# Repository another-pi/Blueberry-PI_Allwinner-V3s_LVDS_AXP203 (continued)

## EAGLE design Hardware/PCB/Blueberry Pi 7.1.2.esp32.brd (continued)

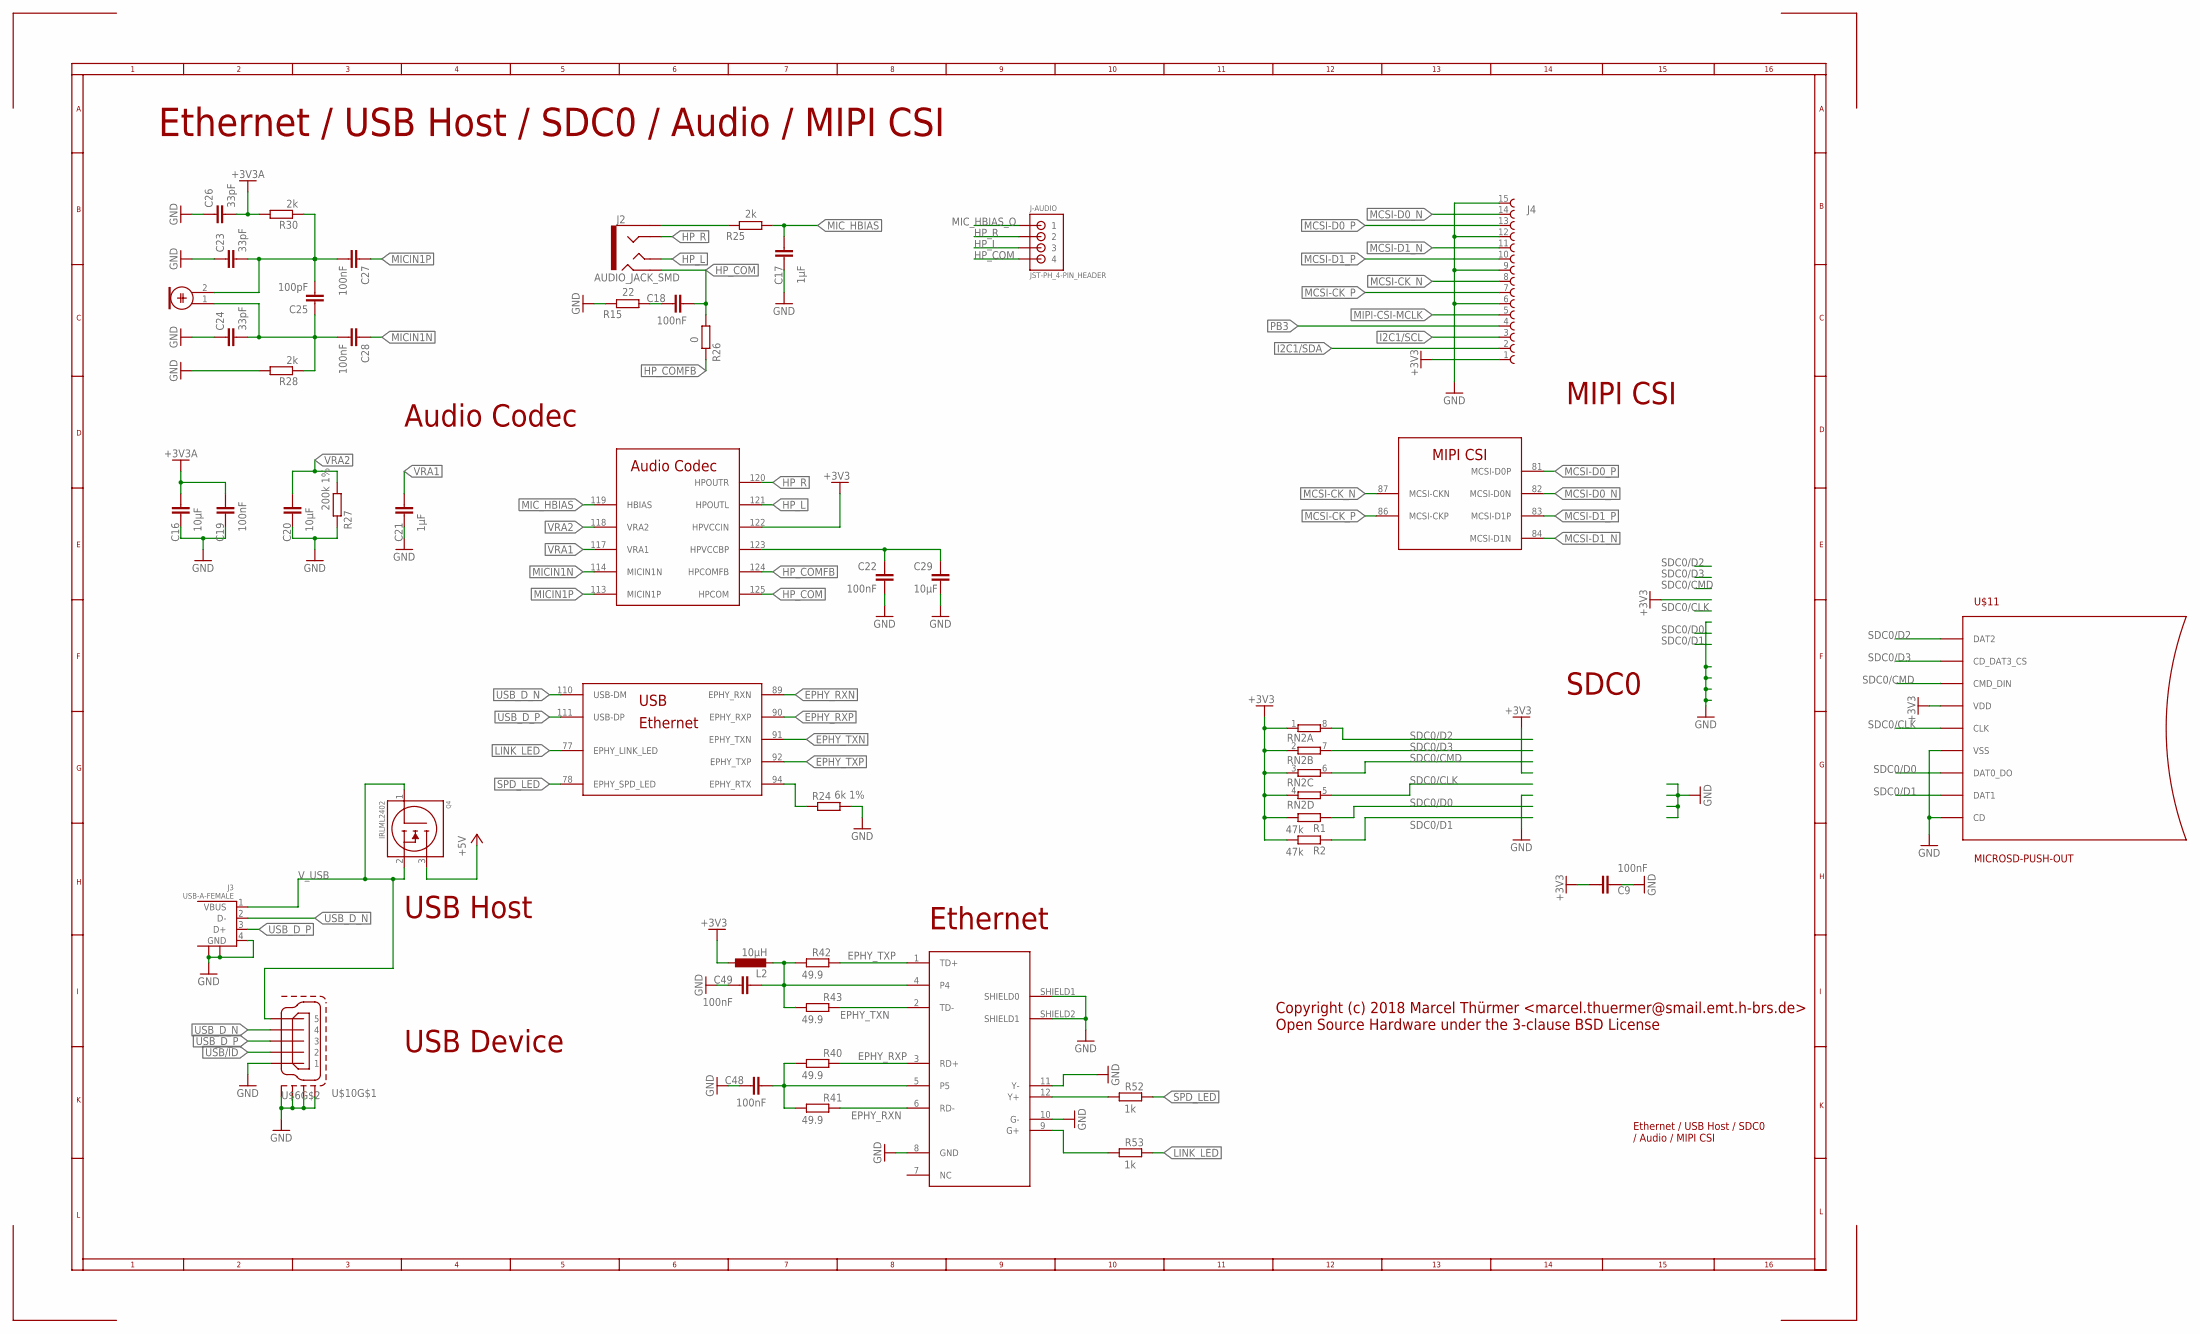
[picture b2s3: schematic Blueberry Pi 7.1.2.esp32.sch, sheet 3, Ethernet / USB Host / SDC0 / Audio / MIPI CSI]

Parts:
C9, C18, C19, C22, C27, C28, C48, C49: 100nF; C0603
C16, C20, C29: 10µF; C0805
C17, C21: 1µF; C0603
C23, C24, C26: 33pF; C0603
C25: 100pF; C0603
J2: AUDIO_JACK_SMD; AUDIO_JACK_3.5MM_TRRS_SMD_RA
J3: USB-A-FEMALE
J4: 68611514122
J-AUDIO: JST-PH_4-PIN_HEADER; JST_B4B-PH_HEADER
L2: 10µH; L0805
MIC: ELECTRET_MICROPHON-F6035AP; F6035AP
Q4: IRLML2402; SOT23
R1, R2: 47k; R0603
R15: 22; R0603
R24: 6k 1%; R0603
R25, R28, R30: 2k; R0603
R26: 0; R0603
R27: 200k 1%; R0603
R40, R41, R42, R43: 49.9; R0603
R52, R53: 1k; R0603
RN2: 4R-NEXB38V; EXB38V
U$1: V3S; QFP-128
U$3: HR911105A; RJ45
U$6, U$10: MICRO-USB-SHIELD-ZX62R-B-5P; ZX62R-B-5P
U$11: MICROSD-PUSH-OUT

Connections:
+3V3: C9.1, J4.1 (15), L2.1, R1.2, R2.2, RN2.1, RN2.2 (1), RN2.3 (1), RN2.4 (1), U$1.122 (HPVCCIN), U$11.4 (VDD); also elsewhere on the board
+3V3A: C16.2, C19.2, C26.2, R30.2; also elsewhere on the board
+5V: Q4.3 (DRAIN); also elsewhere on the board
EPHY_RXN: R41.1, U$1.89 (EPHY_RXN), U$3.6 (RD-)
EPHY_RXP: R40.1, U$1.90 (EPHY_RXP), U$3.3 (RD+)
EPHY_TXN: R43.1, U$1.91 (EPHY_TXN), U$3.2 (TD-)
EPHY_TXP: R42.1, U$1.92 (EPHY_TXP), U$3.1 (TD+)
GND: C9.2, C16.1, C17.2, C19.1, C20.1, C21.1, C22.2, C23.1, C24.1, C26.1, C29.1, C48.2, C49.2, J3.4 (GND), J3.P$1, J3.P$2, J4.6 (10), J4.9 (7), J4.12 (4), J4.15 (1), R15.1, R24.2, R27.1, R28.2, U$3.8 (GND), U$3.10 (G-), U$3.11 (Y-), U$3.SHIELD1 (SHIELD0), U$3.SHIELD2 (SHIELD1), U$6.1, U$10.M1 (S1), U$10.M2 (S2), U$10.M3 (S3), U$10.M4 (S4), U$11.6 (VSS), U$11.CD, U$11.G1 (VSS), U$11.G2 (VSS), U$11.G3 (VSS), U$11.G4 (VSS); also elsewhere on the board
HP_COM: C18.2, J2.RING2, J-AUDIO.P4 (4), R26.2, U$1.125 (HPCOM)
HP_COMFB: R26.1, U$1.124 (HPCOMFB)
HP_L: J2.TIP, J-AUDIO.P3 (3), U$1.121 (HPOUTL)
HP_R: J2.RING1, J-AUDIO.P2 (2), U$1.120 (HPOUTR)
I2C1/SCL: J4.3 (13); also elsewhere on the board
I2C1/SDA: J4.2 (14); also elsewhere on the board
LINK_LED: R53.1, U$1.77 (EPHY_LINK_LED)
MCSI-CK_N: J4.8, U$1.87 (MCSI-CKN)
MCSI-CK_P: J4.7 (9), U$1.86 (MCSI-CKP)
MCSI-D0_N: J4.14 (2), U$1.82 (MCSI-D0N)
MCSI-D0_P: J4.13 (3), U$1.81 (MCSI-D0P)
MCSI-D1_N: J4.11 (5), U$1.84 (MCSI-D1N)
MCSI-D1_P: J4.10 (6), U$1.83 (MCSI-D1P)
MICIN1N: C28.1, U$1.114 (MICIN1N)
MICIN1P: C27.1, U$1.113 (MICIN1P)
MIC_HBIAS: C17.1, R25.2, U$1.119 (HBIAS)
MIC_HBIAS_O: J2.EARTH, J-AUDIO.P1 (1), R25.1
MIPI-CSI-MCLK: J4.5 (11); also elsewhere on the board
unnamed: R24.1, U$1.94 (EPHY_RTX)
unnamed: R53.2, U$3.9 (G+)
unnamed: R52.2, U$3.12 (Y+)
unnamed: C49.1, L2.2, R42.2, R43.2, U$3.4
unnamed: C48.1, R40.2, R41.2, U$3.5
unnamed: C22.1, C29.2, U$1.123 (HPVCCBP)
unnamed: C18.1, R15.2
unnamed: C23.2, C25.2, C27.2, MIC.2, R30.1
unnamed: C24.2, C25.1, C28.2, MIC.1, R28.1
PB3: J4.4 (12); also elsewhere on the board
SDC0/CLK: RN2.5 (2), U$11.5 (CLK); also elsewhere on the board
SDC0/CMD: RN2.6 (2), U$11.3 (CMD_DIN); also elsewhere on the board
SDC0/D0: R1.1, U$11.7 (DAT0_DO); also elsewhere on the board
SDC0/D1: R2.1, U$11.8 (DAT1); also elsewhere on the board
SDC0/D2: RN2.8 (2), U$11.1 (DAT2); also elsewhere on the board
SDC0/D3: RN2.7 (2), U$11.2 (CD_DAT3_CS); also elsewhere on the board
SPD_LED: R52.1, U$1.78 (EPHY_SPD_LED)
USB/ID: U$6.2; also elsewhere on the board
USB_D_N: J3.2 (D-), U$1.110 (USB-DM), U$6.4
USB_D_P: J3.3 (D+), U$1.111 (USB-DP), U$6.3
VRA1: C21.2, U$1.117 (VRA1)
VRA2: C20.2, R27.2, U$1.118 (VRA2)
V_USB: J3.1 (VBUS), Q4.1 (GATE), Q4.2 (SOURCE), U$6.5

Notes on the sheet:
Ethernet / USB Host / SDC0 / Audio / MIPI CSI
USB Host
Audio Codec
MIPI CSI
Ethernet
SDC0
Copyright (c) 2018 Marcel Thürmer <marcel.thuermer@smail.emt.h-brs.de> Open Source Hardware under the 3-clause BSD License
USB Device
Ethernet / USB Host / SDC0 / Audio / MIPI CSI

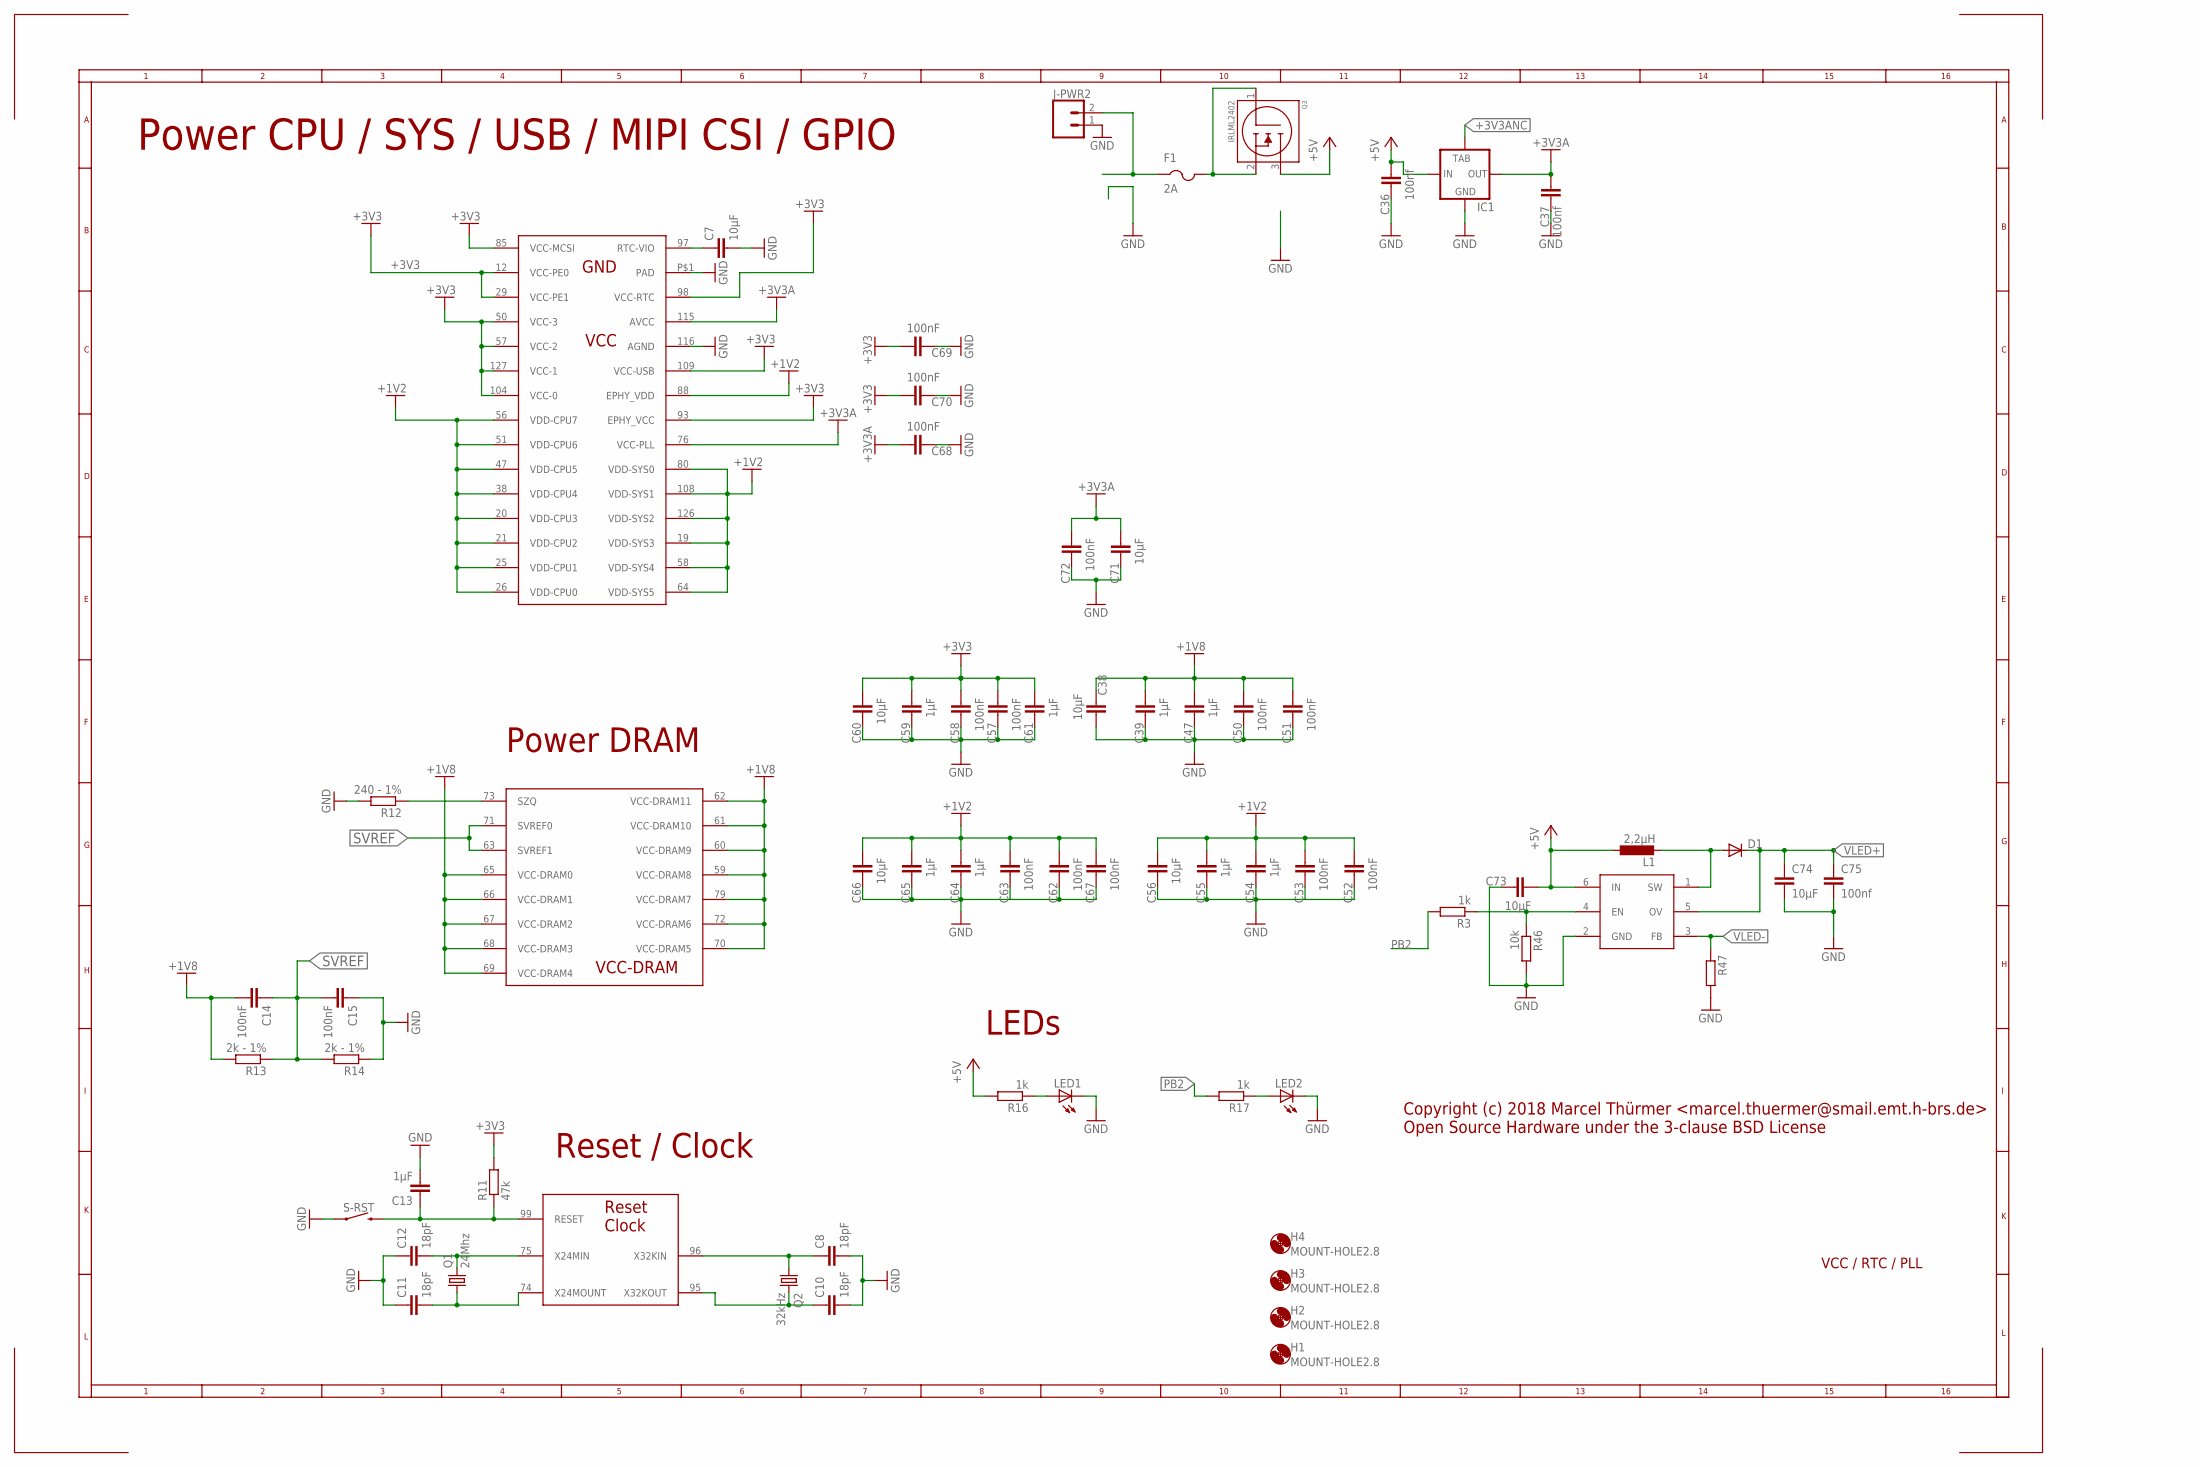
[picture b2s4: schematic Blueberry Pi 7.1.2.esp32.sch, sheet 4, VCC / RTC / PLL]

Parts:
C7, C66, C73, C74: 10µF; C0805
C8, C10, C11, C12: 18pF; C0603
C13, C39, C47, C55, C64, C65: 1µF; C0603
C14, C15, C51, C53, C57, C58, C62, C67, C68, C70, C72: 100nF; C0603
C36, C37, C75: 100nf; C0603
C38, C56, C60, C71: 10µF; C0603
C50, C52, C63, C69: 100nF; C0805
C54, C59, C61: 1µF; C0805
D1: DIODE-SOD323-W; SOD323-W
F1: 2A; R1206
H1, H2, H3, H4: MOUNT-HOLE2.8; 2,8
IC1: LM1117; SOT223
J-PWR2: CONN_02; 1X02
L1: 2,2µH; ODD-INDUCTOR
LED1, LED2: LEDCHIPLED_0805; CHIPLED_0805
Q1: 24Mhz; HC49U-V
Q2: 32kHz; TC38H
Q3: IRLML2402; SOT23
R3, R16, R17: 1k; R0603
R11: 47k; R0603
R12: 240 - 1%; R0603
R13, R14: 2k - 1%; R0603
R46: 10k; R0603
R47: R-EU_R0603; R0603
S-RST: SPARKFUN-SWITCHES_MOMENTARY-SWITCH-SPST-SMD-5.2-R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; SPARKFUN-SWITCHES_TACTILE_SWITCH_SMD_5.2MM
U$1: V3S; QFP-128
U$9: PT4101; SOT23-6

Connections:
5VNS: F1.1, J-PWR2.2
+1V2: C52.1, C53.1, C54.1, C55.1, C56.1, C62.1, C63.1, C64.1, C65.1, C66.1, C67.1, U$1.19 (VDD-SYS3), U$1.20 (VDD-CPU3), U$1.21 (VDD-CPU2), U$1.25 (VDD-CPU1), U$1.26 (VDD-CPU0), U$1.38 (VDD-CPU4), U$1.47 (VDD-CPU5), U$1.51 (VDD-CPU6), U$1.56 (VDD-CPU7), U$1.58 (VDD-SYS4), U$1.64 (VDD-SYS5), U$1.80 (VDD-SYS0), U$1.88 (EPHY_VDD), U$1.108 (VDD-SYS1), U$1.126 (VDD-SYS2); also elsewhere on the board
+1V8: C14.2, C38.2, C39.1, C47.1, C50.1, C51.1, R13.2, U$1.59 (VCC-DRAM8), U$1.60 (VCC-DRAM9), U$1.61 (VCC-DRAM10), U$1.62 (VCC-DRAM11), U$1.65 (VCC-DRAM0), U$1.66 (VCC-DRAM1), U$1.67 (VCC-DRAM2), U$1.68 (VCC-DRAM3), U$1.69 (VCC-DRAM4), U$1.70 (VCC-DRAM5), U$1.72 (VCC-DRAM6), U$1.79 (VCC-DRAM7); also elsewhere on the board
+3V3: C57.1, C58.1, C59.1, C60.1, C61.1, C69.1, C70.1, R11.2, U$1.12 (VCC-PE0), U$1.29 (VCC-PE1), U$1.50 (VCC-3), U$1.57 (VCC-2), U$1.85 (VCC-MCSI), U$1.93 (EPHY_VCC), U$1.98 (VCC-RTC), U$1.104 (VCC-0), U$1.109 (VCC-USB), U$1.127 (VCC-1); also elsewhere on the board
+3V3A: C37.1, C68.1, C71.1, C72.1, IC1.2 (OUT), U$1.76 (VCC-PLL), U$1.115 (AVCC); also elsewhere on the board
+3V3ANC: IC1.4 (IN1)
+5V: C36.1, C73.1, IC1.3 (IN), L1.P$1 (1), Q3.3 (DRAIN), R16.2, U$9.6 (IN); also elsewhere on the board
GND: C7.2, C8.2, C10.2, C11.1, C12.1, C13.2, C15.1, C36.2, C37.2, C38.1, C39.2, C47.2, C50.2, C51.2, C52.2, C53.2, C54.2, C55.2, C56.2, C57.2, C58.2, C59.2, C60.2, C61.2, C62.2, C63.2, C64.2, C65.2, C66.2, C67.2, C68.2, C69.2, C70.2, C71.2, C72.2, C73.2, C74.2, C75.2, IC1.1 (GND), J-PWR2.1, LED1.C, LED2.C, R12.2, R14.1, R46.2, R47.2, S-RST.1, S-RST.2 (1), U$1.116 (AGND), U$1.P$1 (PAD), U$9.2 (GND); also elsewhere on the board
unnamed: LED1.A, R16.1
unnamed: LED2.A, R17.1
unnamed: R3.1, R46.1, U$9.4 (EN)
unnamed: D1.A, L1.P$2 (2), U$9.1 (SW)
unnamed: C7.1, U$1.97 (RTC-VIO)
unnamed: C10.1, Q2.2, U$1.95 (X32KOUT)
unnamed: C8.1, Q2.1, U$1.96 (X32KIN)
unnamed: C11.2, Q1.1, U$1.74 (X24MOUNT)
unnamed: C12.2, Q1.2, U$1.75 (X24MIN)
unnamed: C13.1, R11.1, S-RST.3 (2), S-RST.4 (2), U$1.99 (RESET)
unnamed: R12.1, U$1.73 (SZQ)
PB2: R3.2, R17.2; also elsewhere on the board
SVREF: C14.1, C15.2, R13.1, R14.2, U$1.63 (SVREF1), U$1.71 (SVREF0)
VLED+: C74.1, C75.1, D1.C, U$9.5 (OV); also elsewhere on the board
VLED-: R47.1, U$9.3 (FB); also elsewhere on the board
V_PWR: F1.2, Q3.1 (GATE), Q3.2 (SOURCE)

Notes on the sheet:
VCC / RTC / PLL
Power CPU / SYS / USB / MIPI CSI / GPIO
Power DRAM
Copyright (c) 2018 Marcel Thürmer <marcel.thuermer@smail.emt.h-brs.de> Open Source Hardware under the 3-clause BSD License
Reset / Clock
LEDs

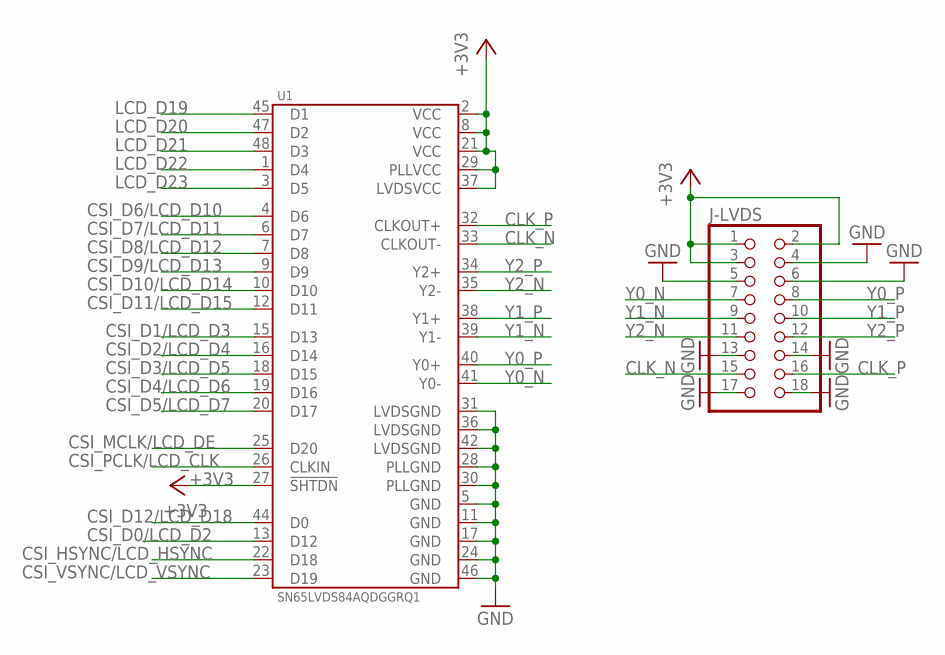
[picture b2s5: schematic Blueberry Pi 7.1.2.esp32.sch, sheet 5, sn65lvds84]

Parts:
J-LVDS: PINHEAD_PINHD-2X9M; PINHEAD_2X09M
U1: SN65LVDS84AQDGGRQ1; TFSOP-48-6.1MM

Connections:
+3V3: J-LVDS.1, J-LVDS.2, J-LVDS.3, U1.2 (VCC), U1.8 (VCC), U1.21 (VCC), U1.27 (!SHTDN), U1.29 (PLLVCC), U1.37 (LVDSVCC); also elsewhere on the board
CLK_N: J-LVDS.15, U1.33 (CLKOUT-)
CLK_P: J-LVDS.16, U1.32 (CLKOUT+)
CSI_D0/LCD_D2: U1.13 (D12); also elsewhere on the board
CSI_D1/LCD_D3: U1.15 (D13); also elsewhere on the board
CSI_D2/LCD_D4: U1.16 (D14); also elsewhere on the board
CSI_D3/LCD_D5: U1.18 (D15); also elsewhere on the board
CSI_D4/LCD_D6: U1.19 (D16); also elsewhere on the board
CSI_D5/LCD_D7: U1.20 (D17); also elsewhere on the board
CSI_D6/LCD_D10: U1.4 (D6); also elsewhere on the board
CSI_D7/LCD_D11: U1.6 (D7); also elsewhere on the board
CSI_D8/LCD_D12: U1.7 (D8); also elsewhere on the board
CSI_D9/LCD_D13: U1.9 (D9); also elsewhere on the board
CSI_D10/LCD_D14: U1.10 (D10); also elsewhere on the board
CSI_D11/LCD_D15: U1.12 (D11); also elsewhere on the board
CSI_D12/LCD_D18: U1.44 (D0); also elsewhere on the board
CSI_HSYNC/LCD_HSYNC: U1.22 (D18); also elsewhere on the board
CSI_MCLK/LCD_DE: U1.25 (D20); also elsewhere on the board
CSI_PCLK/LCD_CLK: U1.26 (CLKIN); also elsewhere on the board
CSI_VSYNC/LCD_VSYNC: U1.23 (D19); also elsewhere on the board
GND: J-LVDS.4, J-LVDS.5, J-LVDS.6, J-LVDS.13, J-LVDS.14, J-LVDS.17, J-LVDS.18, U1.5 (GND), U1.11 (GND), U1.17 (GND), U1.24 (GND), U1.28 (PLLGND), U1.30 (PLLGND), U1.31 (LVDSGND), U1.36 (LVDSGND), U1.42 (LVDSGND), U1.46 (GND); also elsewhere on the board
LCD_D19: U1.45 (D1); also elsewhere on the board
LCD_D20: U1.47 (D2); also elsewhere on the board
LCD_D21: U1.48 (D3); also elsewhere on the board
LCD_D22: U1.1 (D4); also elsewhere on the board
LCD_D23: U1.3 (D5); also elsewhere on the board
Y0_N: J-LVDS.7, U1.41 (Y0-)
Y0_P: J-LVDS.8, U1.40 (Y0+)
Y1_N: J-LVDS.9, U1.39 (Y1-)
Y1_P: J-LVDS.10, U1.38 (Y1+)
Y2_N: J-LVDS.11, U1.35 (Y2-)
Y2_P: J-LVDS.12, U1.34 (Y2+)

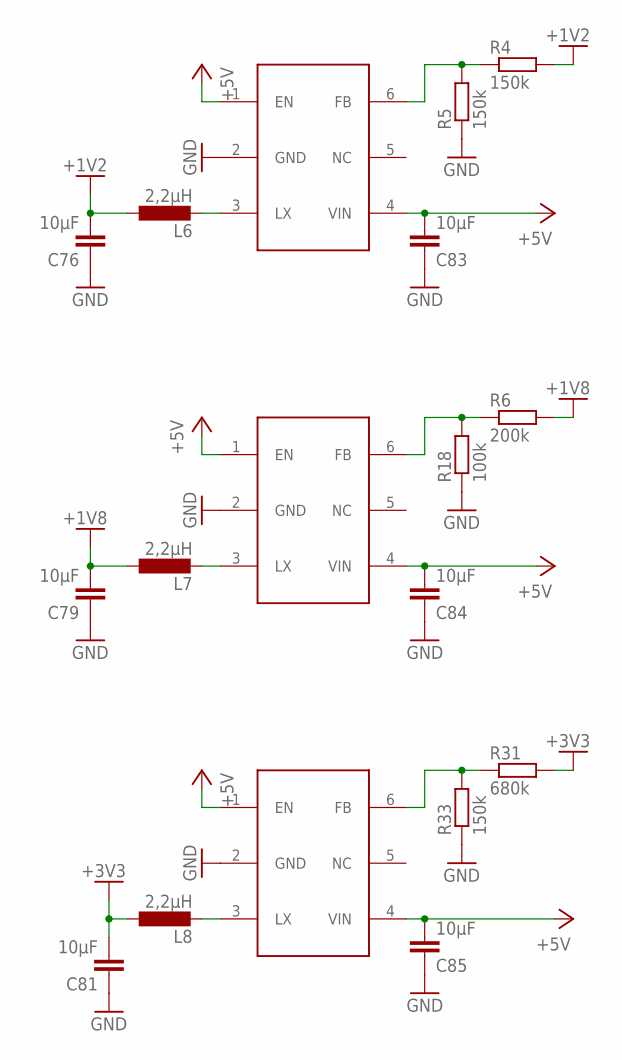
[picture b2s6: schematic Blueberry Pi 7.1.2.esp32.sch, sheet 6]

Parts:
C76, C79, C81, C83, C84, C85: 10µF; C0805
L6, L7, L8: 2,2µH; ODD-INDUCTOR
R4, R5, R33: 150k; R0603
R6: 200k; R0603
R18: 100k; R0603
R31: 680k; R0603
U$5, U$12, U$13: STI3411; SOT23-6

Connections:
+1V2: C76.2, L6.P$1 (1), R4.2; also elsewhere on the board
+1V8: C79.2, L7.P$1 (1), R6.2; also elsewhere on the board
+3V3: C81.2, L8.P$1 (1), R31.2; also elsewhere on the board
+5V: C83.2, C84.2, C85.2, U$5.1 (EN), U$5.4 (VIN), U$12.1 (EN), U$12.4 (VIN), U$13.1 (EN), U$13.4 (VIN); also elsewhere on the board
GND: C76.1, C79.1, C81.1, C83.1, C84.1, C85.1, R5.1, R18.1, R33.1, U$5.2 (GND), U$12.2 (GND), U$13.2 (GND); also elsewhere on the board
unnamed: L6.P$2 (2), U$13.3 (LX)
unnamed: L7.P$2 (2), U$5.3 (LX)
unnamed: R4.1, R5.2, U$13.6 (FB)
unnamed: L8.P$2 (2), U$12.3 (LX)
unnamed: R6.1, R18.2, U$5.6 (FB)
unnamed: R31.1, R33.2, U$12.6 (FB)

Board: 2 copper layers, 163 parts (94 on the bottom side), 137 nets, no tracks yet.

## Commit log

2018-09-03 added LVDS serialiser SN65LVDS84
2018-09-03 w25q128, tsc2003, TF slot. README
2018-09-04 a PCB with AXP203 power was added (without EA3036). may be powered from a Li-battery
2018-09-12 tracing of BBPi*AXP203 was upbated
2019-03-03 better power driwers, ESP32 as a WiFi/BLE controller, list of LCDs
2019-03-13 added Blueberry Pi 7.1.2.esp32.no-lan. see Readme.md
2019-03-17 added onboard li-ion/polimer battery charger, and step-up circuits for power from a li-battery.
2019-03-20 added capacitive touch socket (not ready yet), other pwr-inductors (CD32), datasheets
2019-03-28 interrupt pin for all touchscreens is PB3 shared with MIPI-CSI cam. basically added SPI-NOR-FLASH in the 16pins package (>= 32MB flashes)
2019-04-01 photo of working framebuffer + touchscreen was added (inferno-os on the photo)
2019-04-08 (not finished yet) checks and new choise with SIM800C gsm module
2019-04-25 switched to `A9G` as a GSM/GPRS/GPS/GNSS module. for now "Blueberry Pi 7.1.2.esp32.no-lan.gsm-a9g" is the main branch. small changes in power and touchscreen sockets
2019-04-28 added new compatible tft models. (ATTENTION! not all of them were checked preciselly!)
2019-06-29 better connected A9G module. added 'no-50pin lcd' schematic easier for router and with headers for the rest of A9G pins
